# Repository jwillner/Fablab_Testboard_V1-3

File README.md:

<!-- Fablab-Winti ESP32-C6-Dev-Projekt – README.md -->
<!-- Einfach als "README.md" im Repository speichern -->

# Fablab-Winti KiCad-ESP32-C6-Projekt  
> **Work-in-progress** – du  layoutest, du lötest, du programmierst  Slack `#fablab-winti`

## 🧰 Hardware-Baukasten (Stand: August 2025)

| Teil | Beschreibung | Kurz-Link |
|---|---|---|
| **ESP32-C6-Zero** (Waveshare) | USB-C, RISC-V, Wi-Fi 6, BLE, Zigbee | [Wiki](https://www.waveshare.com/wiki/ESP32-C6-Zero) |
| **ESP32-C6-Dev-Kit-N8** | Pin-kompatibel, 8 MB Flash | [Wiki](https://www.waveshare.com/wiki/ESP32-C6-DEV-KIT-N8) |
| **1,69" TFT 240×280 ST7789** | SPI, 3,3 V, abgerundete Ecken | [AZ-Delivery](https://www.az-delivery.de/products/1-69-zoll-tft-display) |
| **2,4" TFT Touch ILI9341** | Größer + Touch, selbe Lib | [AZ-Delivery](https://www.az-delivery.de/products/2-4-tft-lcd-touch-display-1) |
| **SIM7080G** | LTE Cat-M & NB-IoT + GNSS | [SIMCom](https://www.simcom.com/product/SIM7080G.html) |

---

## 📂 KiCad-Projekt öffnen

```bash
git clone https://github.com/jwillner/Fablab_Testboard_V1-3.git
cd Fablab_Testboard_V1-3
kicad Fablab_Testboard_V1-3.kicad_pro   # Schema + PCB + 3D sofort sichtbar

#Beispiel Software-Projekte
| Repo                                                                       | Funktion                                    | Status                 |
| -------------------------------------------------------------------------- | ------------------------------------------- | ---------------------- |
| [**ESP32-C6-HelloWorld**](https://github.com/jwillner/ESP32-C6-HelloWorld) | LED blinkt, UART loggt → Erststart-Template | ✅ lauffähig            |
| [**ESP32-C6-UART0**](https://github.com/jwillner/ESP32-C6-UART0)           | Bidirektionale UART-Bridge + Echo-Test      | 🔄 Review gesucht      |
| [**ESP32-C6-TFT191-V1**](https://github.com/jwillner/ESP32-C6-TFT191-V1)   | 1,69" TFT Grundgrafik (ST7789)              | 🔄 Optimierung offen   |
| [**ESP32-C6-TFT191-V2**](https://github.com/jwillner/ESP32-C6-TFT191-V2)   | 1,69" TFT + Touch + SD-Card                 | 🚧 Work-in-Progress    |
| **BME280-C6** *(coming)*                                                   | Temperatur / Luftfeuchte / Druck per MQTT   | 🔍 Mitstreiter gesucht |
| **ICM-20948-C6** *(coming)*                                                | 9-DoF IMU → Lage-/Bewegungs-Logger          | 🔍 Mitstreiter gesucht |
| **SIM7080G-C6-GNSS** *(coming)*                                            | LTE-M Upload + GNSS-Tracking                | 🔍 Mitstreiter gesucht |

Du willst mithelfen? Einfach im jeweiligen Repo ein Issue aufmachen oder direkt einen Branch pushen!
🎤 Feedback & Mitmachen
Slack: #fablab-winti
Issues: wenn’s qualmt, Ticket aufmachen
PRs: wenn’s läuft, teilen
Lizenz
Hardware CERN-OHL-S v2 • Software MIT

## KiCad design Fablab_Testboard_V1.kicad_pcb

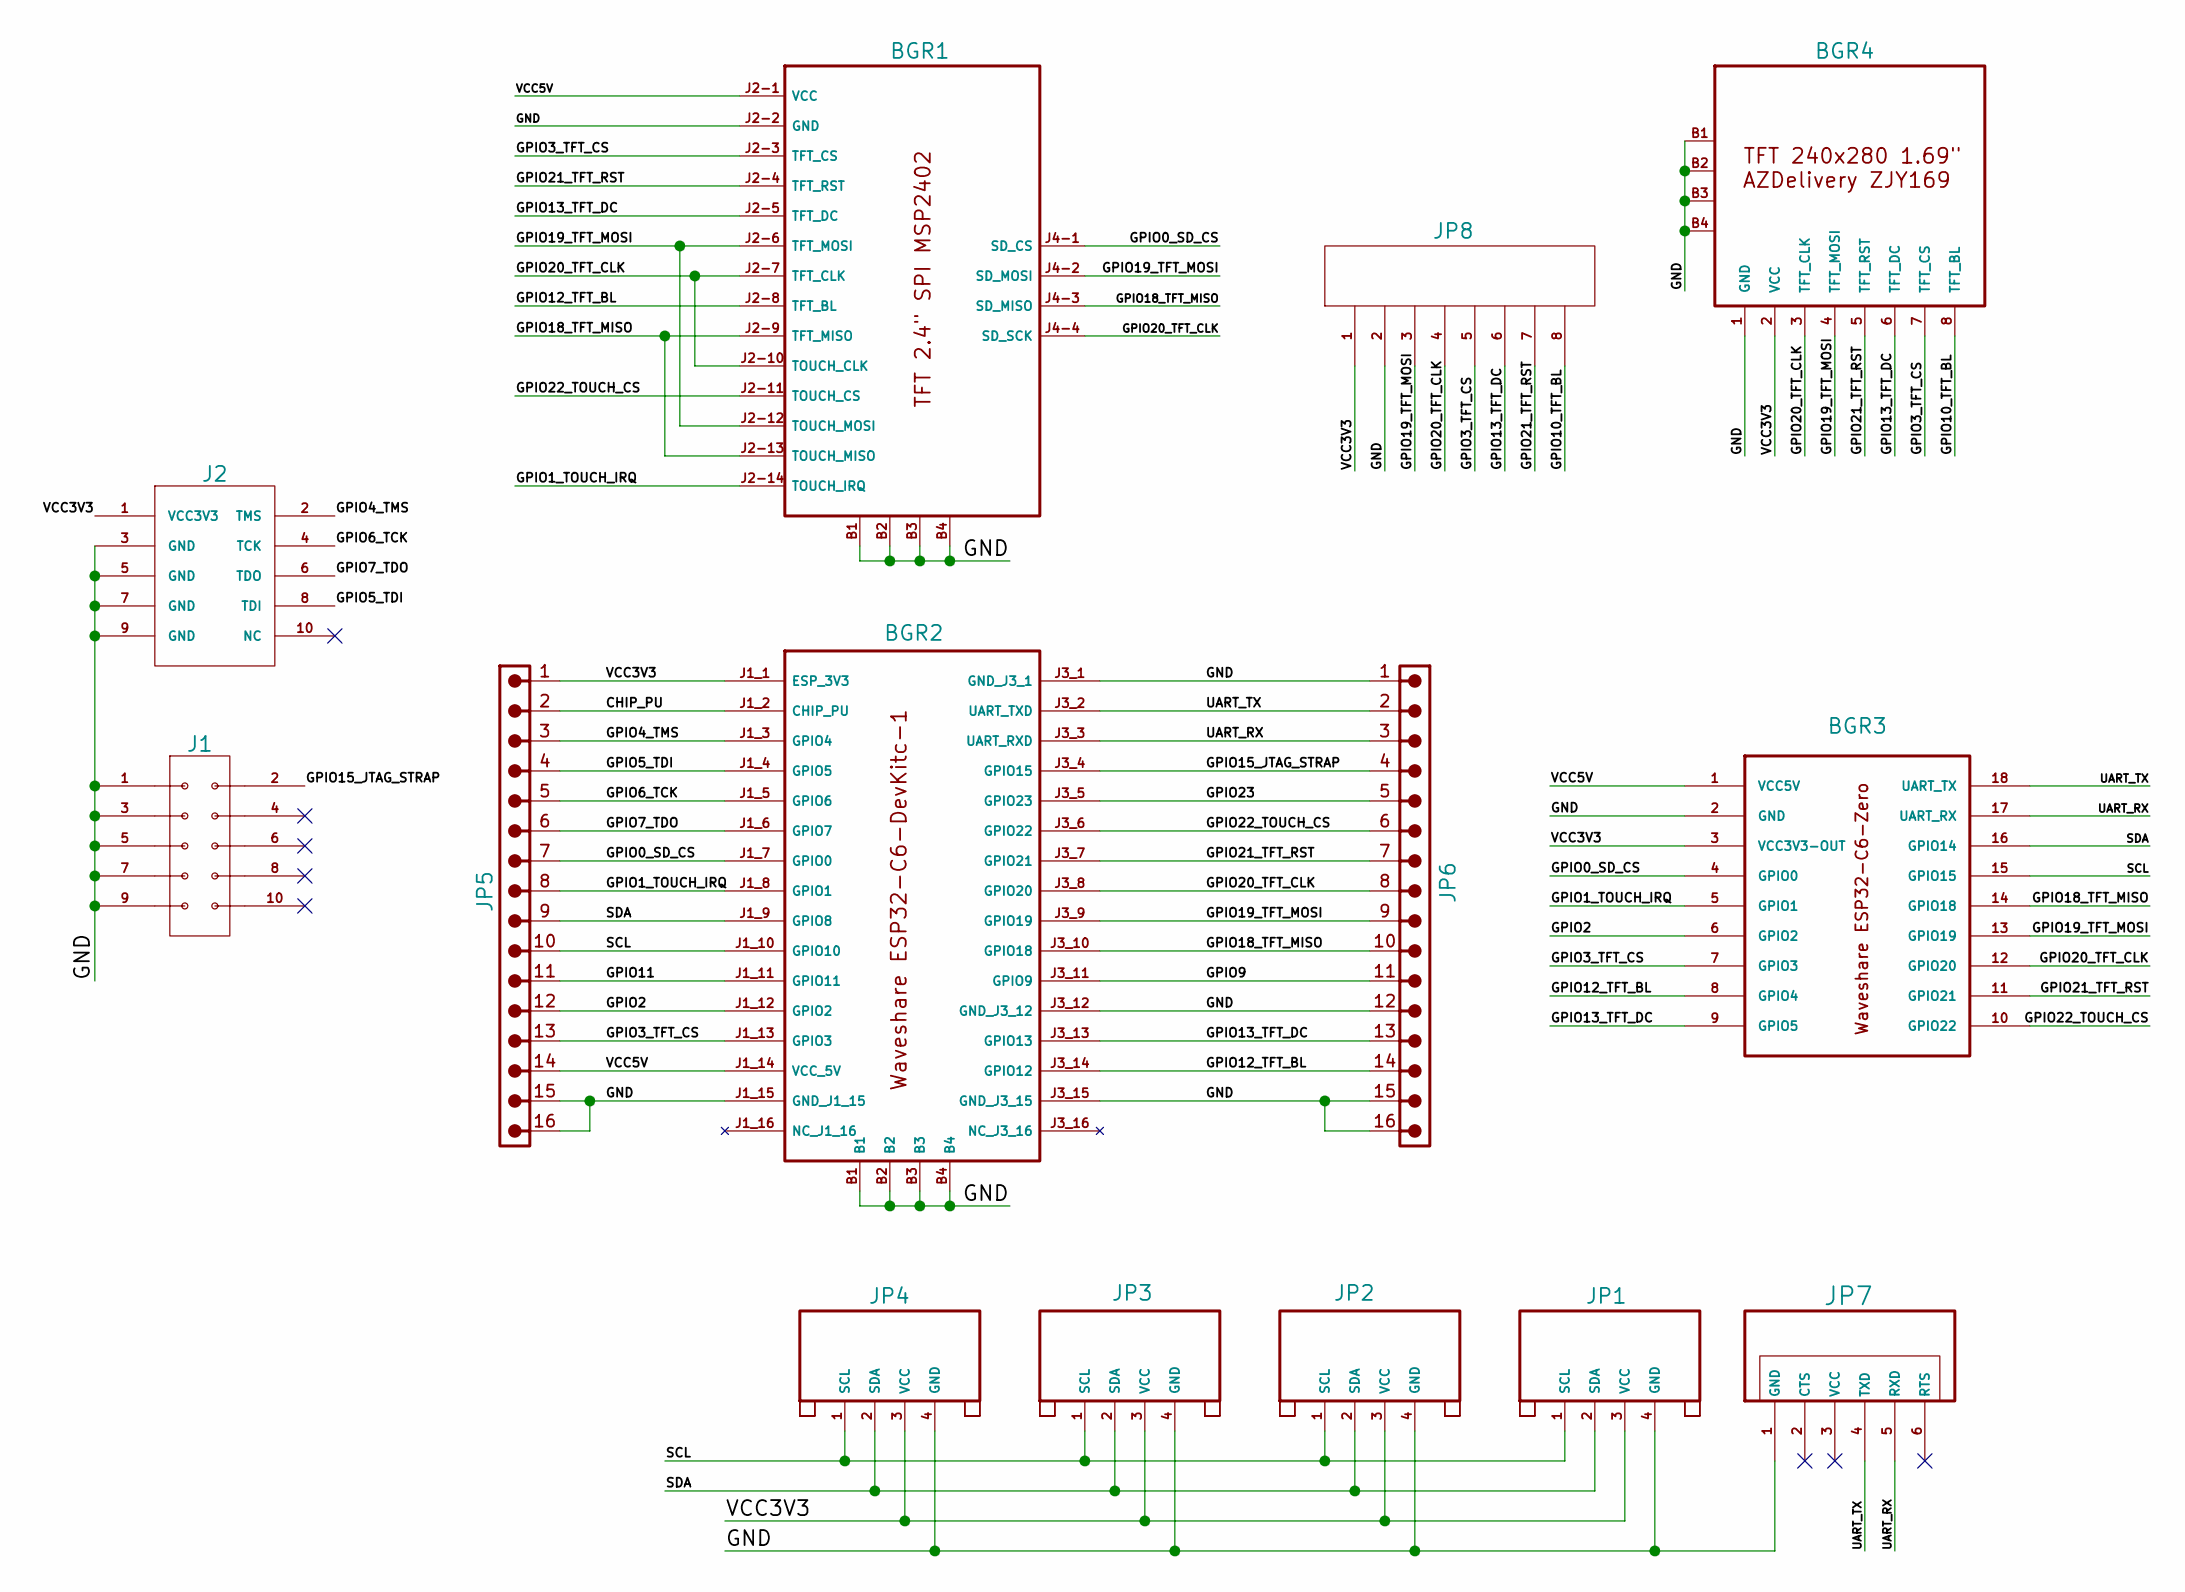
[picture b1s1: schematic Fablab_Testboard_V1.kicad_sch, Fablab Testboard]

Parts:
BGR1: 2.4inch_SPI_Module_ILI9341_SKU_MSP2402
BGR2: MODULE_ESP32-C6-DEVKITC-1-N8
BGR3: WS-ESP32-C3-ZERO; WS_ESP32-C3_ZERO
BGR4: AZDELIVERY-ZJY169; ZJY169-AZDELIVERY
J1: MOLEX-901310765; PARTREV J
J2: SBH11-PBPC-D05-ST-BK; SULLINS_SBH11-PBPC-D05-ST-BK; PARTREV J
JP1, JP2, JP3, JP4: SEEED_110990030
JP5, JP6: WUERTH_61301611121; WUERTH-61301611121
JP7: Molex-705430040; Molex-0705430040
JP8: B10B-PH-K-S_LF__SN_; JST_B8B-PH-K-S; PARTREV JP

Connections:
/CHIP_PU: BGR2.J1_2 (CHIP_PU), JP5.2
/GND: BGR1.B1, BGR1.B2, BGR1.B3, BGR1.B4, BGR1.J2-2 (GND), BGR2.B1, BGR2.B2, BGR2.B3, BGR2.B4, BGR2.J1_15 (GND_J1_15), BGR2.J3_1 (GND_J3_1), BGR2.J3_12 (GND_J3_12), BGR2.J3_15 (GND_J3_15), BGR3.2 (GND), BGR4.1 (GND), BGR4.B1, BGR4.B2, BGR4.B3, BGR4.B4, J1.1, J1.3, J1.5, J1.7, J1.9, J2.3 (GND), J2.5 (GND), J2.7 (GND), J2.9 (GND), JP1.4 (GND), JP2.4 (GND), JP3.4 (GND), JP4.4 (GND), JP5.15, JP5.16, JP6.1, JP6.12, JP6.15, JP6.16, JP7.1 (GND), JP8.2
/GPIO0_SD_CS: BGR1.J4-1 (SD_CS), BGR2.J1_7 (GPIO0), BGR3.4 (GPIO0), JP5.7
/GPIO1_TOUCH_IRQ: BGR1.J2-14 (TOUCH_IRQ), BGR2.J1_8 (GPIO1), BGR3.5 (GPIO1), JP5.8
/GPIO2: BGR2.J1_12 (GPIO2), BGR3.6 (GPIO2), JP5.12
/GPIO3_TFT_CS: BGR1.J2-3 (TFT_CS), BGR2.J1_13 (GPIO3), BGR3.7 (GPIO3), BGR4.7 (TFT_CS), JP5.13, JP8.5
/GPIO4_TMS: BGR2.J1_3 (GPIO4), J2.2 (TMS), JP5.3
/GPIO5_TDI: BGR2.J1_4 (GPIO5), J2.8 (TDI), JP5.4
/GPIO6_TCK: BGR2.J1_5 (GPIO6), J2.4 (TCK), JP5.5
/GPIO7_TDO: BGR2.J1_6 (GPIO7), J2.6 (TDO), JP5.6
/GPIO9: BGR2.J3_11 (GPIO9), JP6.11
/GPIO10_TFT_BL: BGR4.8 (TFT_BL), JP8.8
/GPIO11: BGR2.J1_11 (GPIO11), JP5.11
/GPIO12_TFT_BL: BGR1.J2-8 (TFT_BL), BGR2.J3_14 (GPIO12), BGR3.8 (GPIO4), JP6.14
/GPIO13_TFT_DC: BGR1.J2-5 (TFT_DC), BGR2.J3_13 (GPIO13), BGR3.9 (GPIO5), BGR4.6 (TFT_DC), JP6.13, JP8.6
/GPIO15_JTAG_STRAP: BGR2.J3_4 (GPIO15), J1.2, JP6.4
/GPIO18_TFT_MISO: BGR1.J2-9 (TFT_MISO), BGR1.J2-13 (TOUCH_MISO), BGR1.J4-3 (SD_MISO), BGR2.J3_10 (GPIO18), BGR3.14 (GPIO18), JP6.10
/GPIO19_TFT_MOSI: BGR1.J2-6 (TFT_MOSI), BGR1.J2-12 (TOUCH_MOSI), BGR1.J4-2 (SD_MOSI), BGR2.J3_9 (GPIO19), BGR3.13 (GPIO19), BGR4.4 (TFT_MOSI), JP6.9, JP8.3
/GPIO20_TFT_CLK: BGR1.J2-7 (TFT_CLK), BGR1.J2-10 (TOUCH_CLK), BGR1.J4-4 (SD_SCK), BGR2.J3_8 (GPIO20), BGR3.12 (GPIO20), BGR4.3 (TFT_CLK), JP6.8, JP8.4
/GPIO21_TFT_RST: BGR1.J2-4 (TFT_RST), BGR2.J3_7 (GPIO21), BGR3.11 (GPIO21), BGR4.5 (TFT_RST), JP6.7, JP8.7
/GPIO22_TOUCH_CS: BGR1.J2-11 (TOUCH_CS), BGR2.J3_6 (GPIO22), BGR3.10 (GPIO22), JP6.6
/GPIO23: BGR2.J3_5 (GPIO23), JP6.5
/SCL: BGR2.J1_10 (GPIO10), BGR3.15 (GPIO15), JP1.1 (SCL), JP2.1 (SCL), JP3.1 (SCL), JP4.1 (SCL), JP5.10
/SDA: BGR2.J1_9 (GPIO8), BGR3.16 (GPIO14), JP1.2 (SDA), JP2.2 (SDA), JP3.2 (SDA), JP4.2 (SDA), JP5.9
/UART_RX: BGR2.J3_3 (UART_RXD), BGR3.17 (UART_RX), JP6.3, JP7.5 (RXD)
/UART_TX: BGR2.J3_2 (UART_TXD), BGR3.18 (UART_TX), JP6.2, JP7.4 (TXD)
/VCC3V3: BGR2.J1_1 (ESP_3V3), BGR3.3 (VCC3V3-OUT), BGR4.2 (VCC), J2.1 (VCC3V3), JP1.3 (VCC), JP2.3 (VCC), JP3.3 (VCC), JP4.3 (VCC), JP5.1, JP8.1
/VCC5V: BGR1.J2-1 (VCC), BGR2.J1_14 (VCC_5V), BGR3.1 (VCC5V), JP5.14

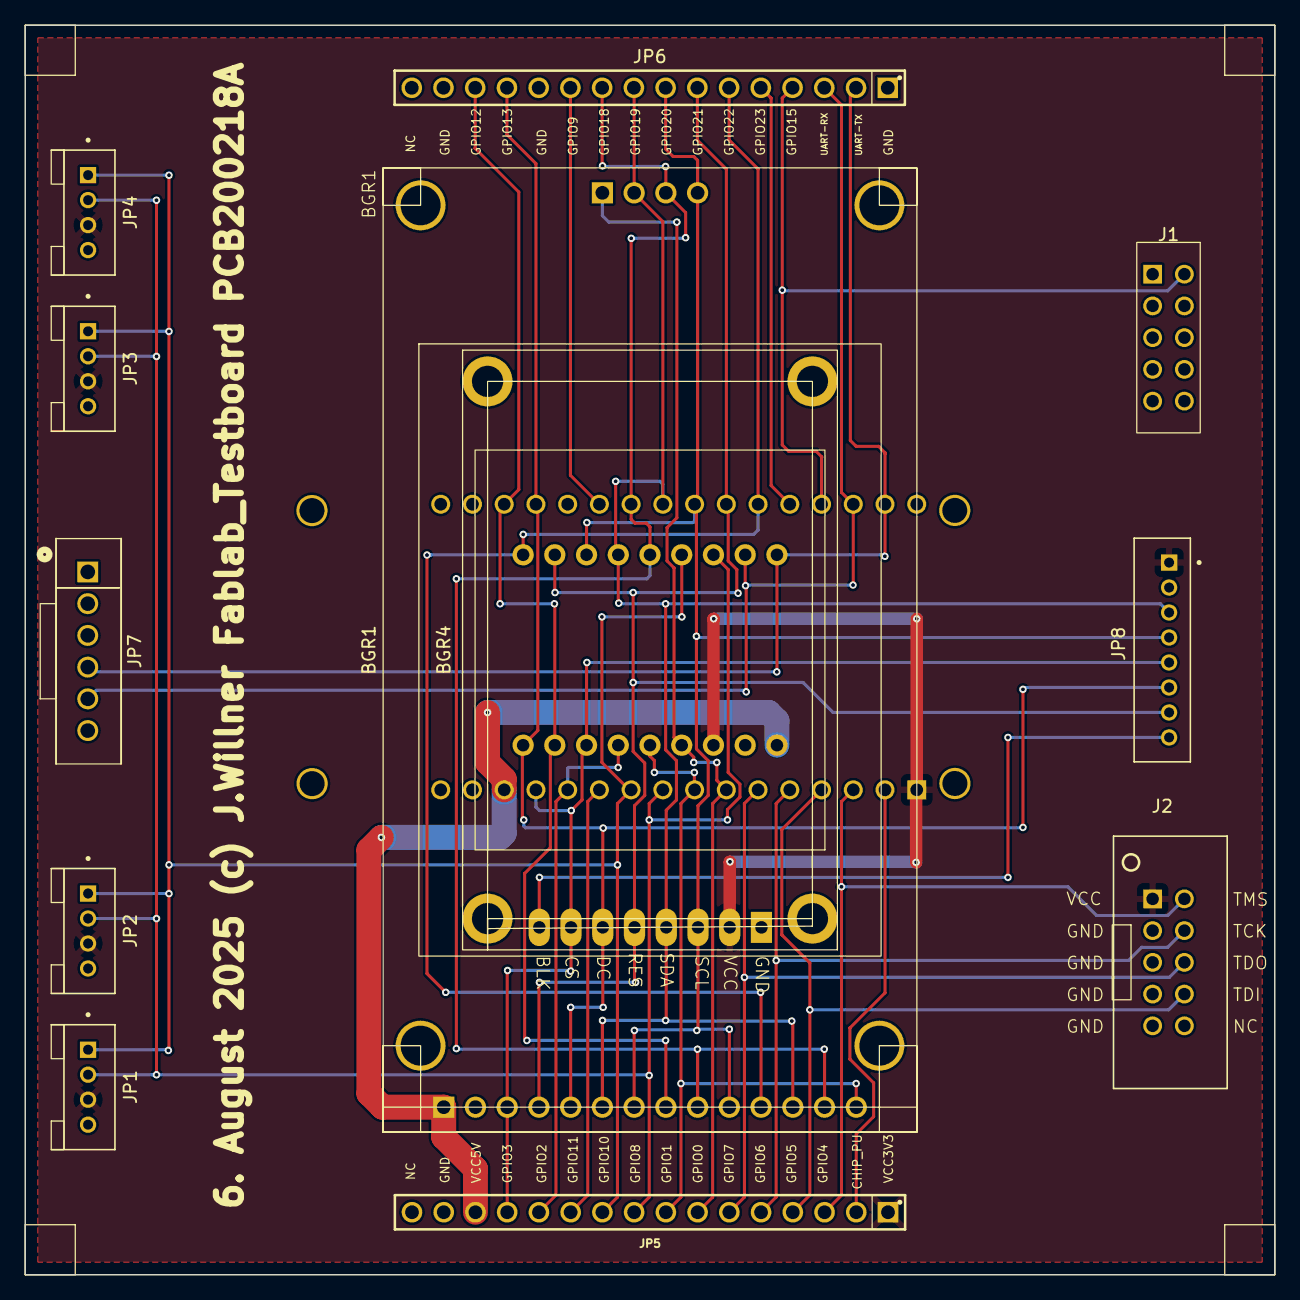
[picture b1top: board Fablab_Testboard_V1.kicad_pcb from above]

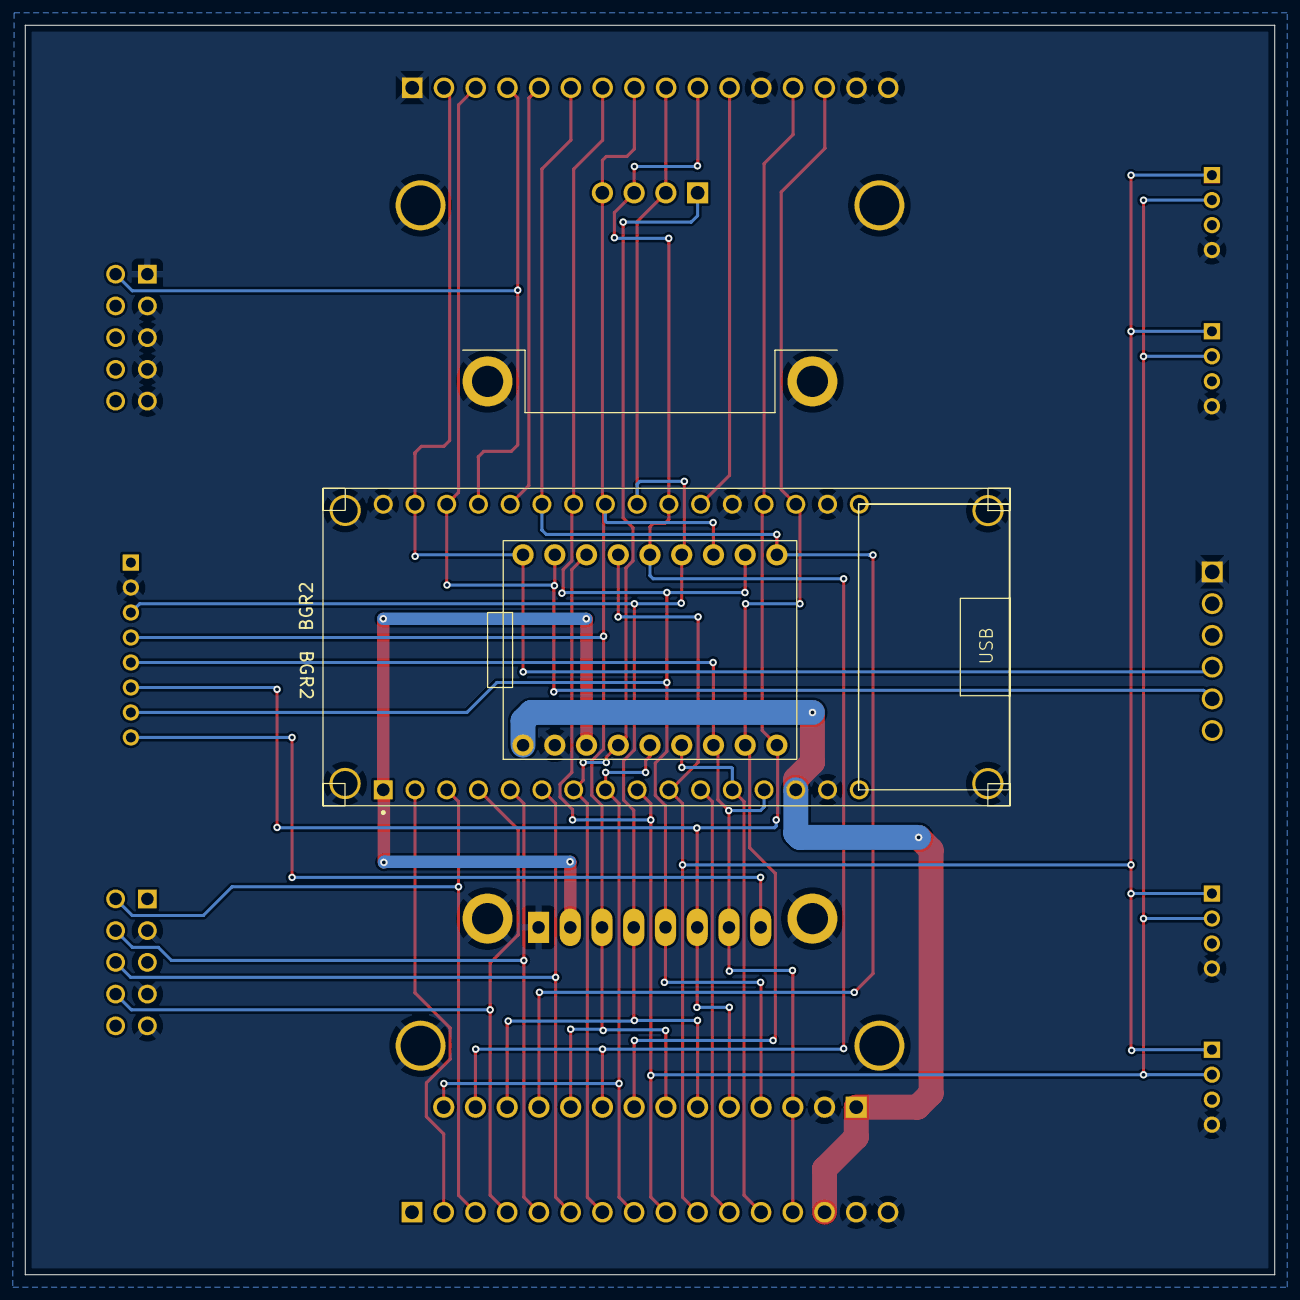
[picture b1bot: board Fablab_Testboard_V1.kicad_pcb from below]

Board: 2 copper layers, 100.0 x 100.0 mm, 14 parts (2 on the bottom side), 28 nets.

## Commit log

2025-08-07 Initial commit of Fablab Testboard V1.3
2025-08-11 zusätzliche Bilder und Silkscreen, plus Bohrlöcher
2025-08-12 neues README.md
2025-08-12 2 neues README.md
2025-08-12 3 neues README.md
2025-08-12 4 neues README.md
